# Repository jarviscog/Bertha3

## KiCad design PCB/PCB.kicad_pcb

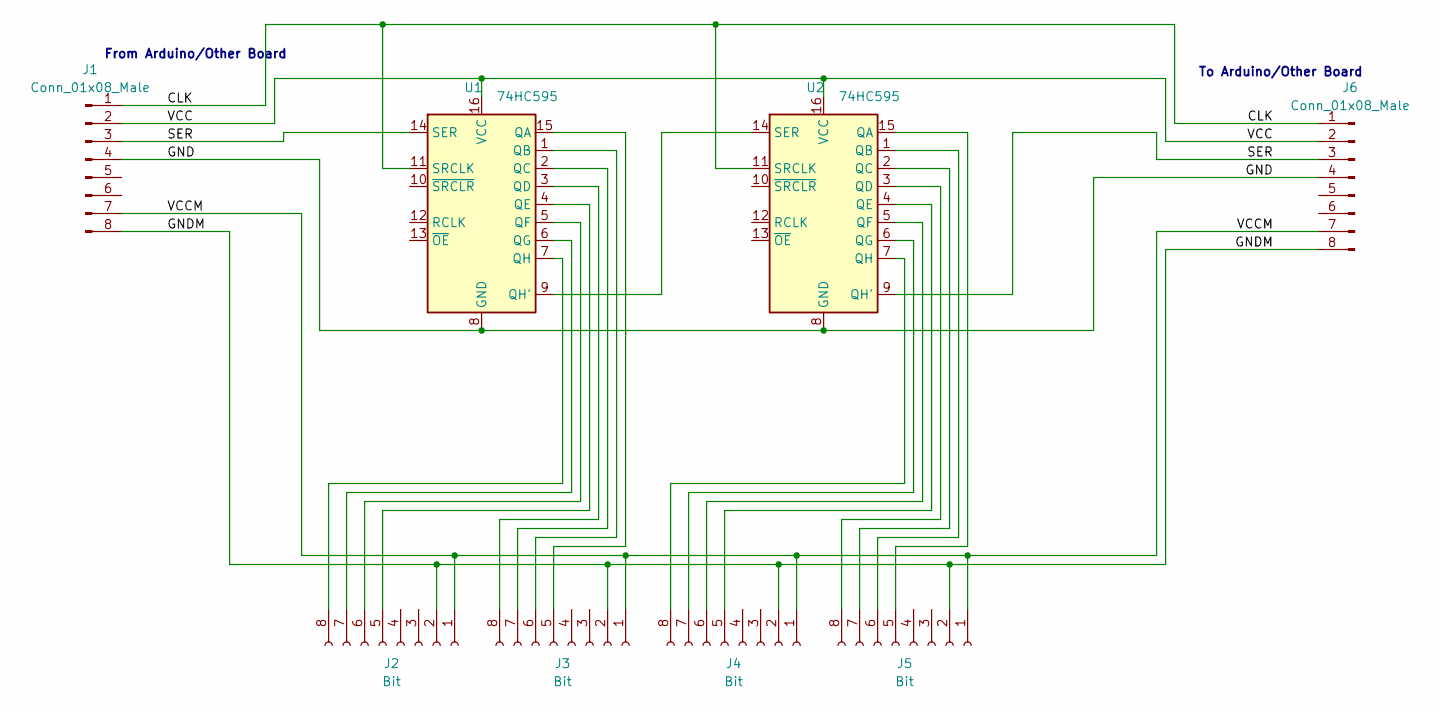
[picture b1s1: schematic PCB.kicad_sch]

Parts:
J1, J6: Conn_01x08_Male; JST_EH_B8B-EH-A_1x08_P2.50mm_Vertical
J2, J3, J4, J5: Bit; JST_EH_B8B-EH-A_1x08_P2.50mm_Vertical
U1, U2: 74HC595; DIP-16_W7.62mm_SMDSocket_SmallPads

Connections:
/CLK: J1.1, J6.1, U1.11 (SRCLK), U2.11 (SRCLK)
/GND: J1.4, J6.4, U1.8 (GND), U2.8 (GND)
/GNDM: J1.8, J2.2, J3.2, J4.2, J5.2, J6.8
/SER: J1.3, J6.3, U1.14 (SER), U2.9 (QH')
/VCC: J1.2, J6.2, U1.16 (VCC), U2.16 (VCC)
/VCCM: J1.7, J2.1, J3.1, J4.1, J5.1, J6.7
unnamed: J2.5, U1.4 (QE)
unnamed: J2.6, U1.5 (QF)
unnamed: J2.7, U1.6 (QG)
unnamed: J2.8, U1.7 (QH)
unnamed: J3.5, U1.15 (QA)
unnamed: J3.6, U1.1 (QB)
unnamed: J3.7, U1.2 (QC)
unnamed: J3.8, U1.3 (QD)
unnamed: J4.5, U2.4 (QE)
unnamed: J4.6, U2.5 (QF)
unnamed: J4.7, U2.6 (QG)
unnamed: J4.8, U2.7 (QH)
unnamed: J5.5, U2.15 (QA)
unnamed: J5.6, U2.1 (QB)
unnamed: J5.7, U2.2 (QC)
unnamed: J5.8, U2.3 (QD)
unnamed: U1.9 (QH'), U2.14 (SER)

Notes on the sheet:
From Arduino/Other Board
To Arduino/Other Board

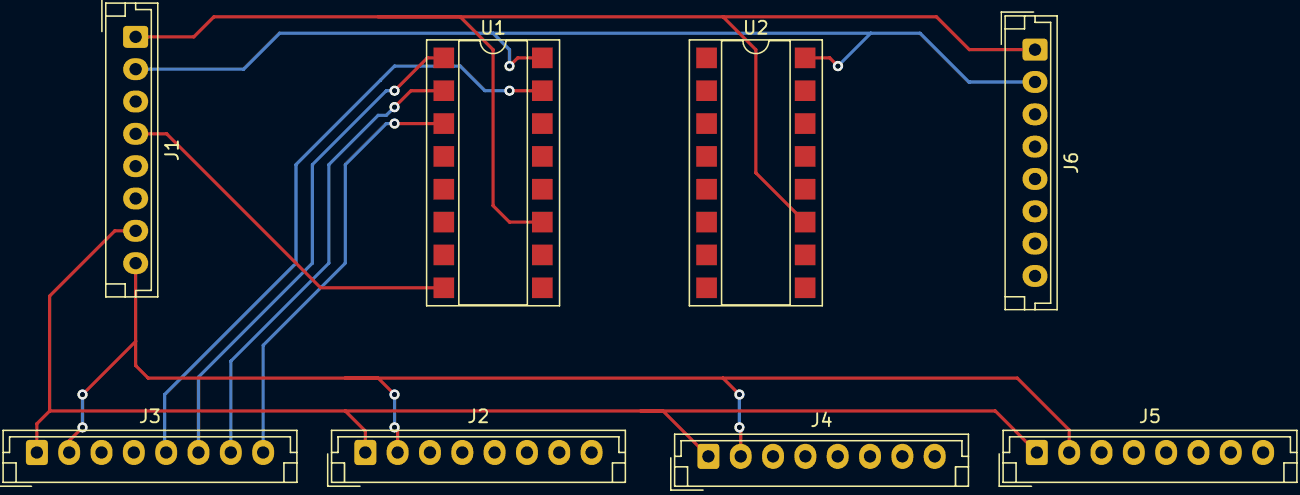
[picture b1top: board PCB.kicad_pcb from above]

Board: 2 copper layers, 8 parts (0 on the bottom side), 23 nets.

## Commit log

2021-03-28 Added all parts from Parts
2021-03-28 Created STL file
2021-03-28 Removed Strange files
2021-04-02 Added More Parts
2021-04-02 Added STL Files for other parts
2021-04-05 Extended box
2021-04-24 Added end cap
2021-04-24 Finished rod end
2021-04-25 Updated STL files
2021-04-25 Fixed stl files for print
2021-04-25 Small Changes
2021-05-02 Made test programs for GPIO pins
2021-05-02 Fixed issues in 3d print
    Changed Stl files
2021-05-19 Fixed tight fitting parts
2021-06-25 New part organization structure pt 1
2021-06-26 New part organization structure pt 2
2021-06-26 Added bit stl file demo
2021-06-26 Added more demo files
2021-06-29 Made Parts printable
2022-04-08 Deleted test cases
2022-04-25 Finished function to print strings to the screen
2022-04-25 Added weather api collector
2022-04-28 Implemented Spotify API
2022-04-28 Updated readme and added TODOs for animations
2022-05-02 Finished print stacked strings
2022-06-14 Updated new bit, and started working on summer version:)
2022-07-11 cleaned up and added new solidworks files
2022-08-08 modified main hole in model
    flaps should now freely fall through the hole and not get stuck on the bottom portion of the front piece.
2022-08-08 made some changes to support a casing for multiple bits
    Created a backplate to hold multiple bits. Also made the material thickness in the models thinner (3mm to 1.5mm)
2022-08-08 deleted some old files
2022-08-08 next iteration of aeroboard model
2022-08-08 cleaned up temp files
2022-08-11 made some models for a new iteration of a position encoder
2022-08-22 Added ESP32 Code
2024-08-19 Enabled autoConnectportal.cpp
